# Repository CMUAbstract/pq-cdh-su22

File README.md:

# Pocketqube Command and Data Handling Board

Pocketqube command and data handling board

**Dependencies**

```bash
sudo apt install build-essential cmake gcc git libusb-1.0-0 libusb-1.0-0-dev libgtk-3-dev
cd $HOME/git-repos/cote/scripts
./setup_dependencies.sh $HOME/sw
```

# Useful link

* [libopencm3](http://libopencm3.org/docs/latest/stm32l4/html/modules.html) : Open source firmware link STM

## Directory Contents

* [3d-models](3d-models/README.md): Contains copies of `.stp` 3D model files
* [components](components/README.md): Contains copies of `.lib` component files
* [datasheets](datasheets/README.md): Contains component datasheets
* [footprints](footprints/README.md): Contains copies of `.kicad_mod` footprint
  files
* [gerbers](gerbers/README.md): Contains the most recent set of Gerber files
* [kicad](kicad/README.md): Contains the KiCad project files
* [versions](versions/README.md): Contains `.zip` files of Gerber files
  submitted for manufacture
* [BOM.csv](BOM.csv): Bill of materials
* [LICENSE](LICENSE): License
* [NOTES.md](NOTES.md): Step-by-step instructions for setting up KiCad,
  designing the board, and exporting Gerber files for manufacture
* [README.md](README.md): This document

## License

Written by Bradley Denby  
Other contributors: None

## Update

PQ-CDH Version 0.1.0 : 

1. Transferred design scheamtic and PCB from Kicad5 to Kicad6
2. Mounting holes adjustment same as referred to comm-401 board.
3. Reduced board dimension 43 x 43 mm
4. Removing 5th Pin from upper and lower right

PQ-CDH Version 0.1.1

1. Changed VDD, GND, SWDIO, and SWCLK to lower left to right 4 pins
2. Changed "PQ CDH v0.1.0" to "PQ CDH v0.1.1"
3. Adjusted controller and Conn_02x06_Odd_Even, for mounting hole clearance.
4. Adjusted Conn_02x06_Odd_Even in vertically aligned along with aligned to top and bottom connector holes.
5. Addition of 4 testpads added between oscillator and its capacitor.

PQ-CDH Version 0.2.0

1. I2C3 SDA and SCL to pins 1 and 2 on the bottom header row
2. ADC to pin 3 on the bottom header row
3. unused GPIO to pins 4 and 5 on bottom header row

See the top-level [LICENSE](LICENSE) file for the license.

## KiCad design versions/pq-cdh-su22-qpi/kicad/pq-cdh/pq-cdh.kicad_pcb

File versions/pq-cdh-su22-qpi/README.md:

# Pocketqube Command and Data Handling Board

Pocketqube command and data handling board

**Dependencies**

```bash
sudo apt install build-essential cmake gcc git libusb-1.0-0 libusb-1.0-0-dev libgtk-3-dev
cd $HOME/git-repos/cote/scripts
./setup_dependencies.sh $HOME/sw
```

## Useful link

* [libopencm3](http://libopencm3.org/docs/latest/stm32l4/html/modules.html) : STM open source firmware link

## Directory Contents

* [3d-models](3d-models/README.md): Contains copies of `.stp` 3D model files
* [components](components/README.md): Contains copies of `.lib` component files
* [datasheets](datasheets/README.md): Contains component datasheets
* [footprints](footprints/README.md): Contains copies of `.kicad_mod` footprint
  files
* [gerbers](gerbers/README.md): Contains the most recent set of Gerber files
* [kicad](kicad/README.md): Contains the KiCad project files
* [versions](versions/README.md): Contains `.zip` files of Gerber files
  submitted for manufacture
* [BOM.csv](BOM.csv): Bill of materials
* [LICENSE](LICENSE): License
* [NOTES.md](NOTES.md): Step-by-step instructions for setting up KiCad,
  designing the board, and exporting Gerber files for manufacture
* [README.md](README.md): This document

## License

Written by Bradley Denby  
Other contributors: None

## Update

PQ-CDH Version 0.1.0 : 

1. Transferred design scheamtic and PCB from Kicad5 to Kicad6
2. Mounting holes adjustment same as referred to comm-401 board.
3. Reduced board dimension 43 x 43 mm
4. Removing 5th Pin from upper and lower right

PQ-CDH Version 0.1.1

1. Changed VDD, GND, SWDIO, and SWCLK to lower left to right 4 pins
2. Changed "PQ CDH v0.1.0" to "PQ CDH v0.1.1"
3. Adjusted controller and Conn_02x06_Odd_Even, for mounting hole clearance.
4. Adjusted Conn_02x06_Odd_Even in vertically aligned along with aligned to top and bottom connector holes.
5. Addition of 4 testpads added between oscillator and its capacitor.

PQ-CDH Version 0.2.0

1. I2C3 SDA and SCL to pins 1 and 2 on the bottom header row
2. ADC to pin 3 on the bottom header row
3. unused GPIO to pins 4 and 5 on bottom header row

See the top-level [LICENSE](LICENSE) file for the license.

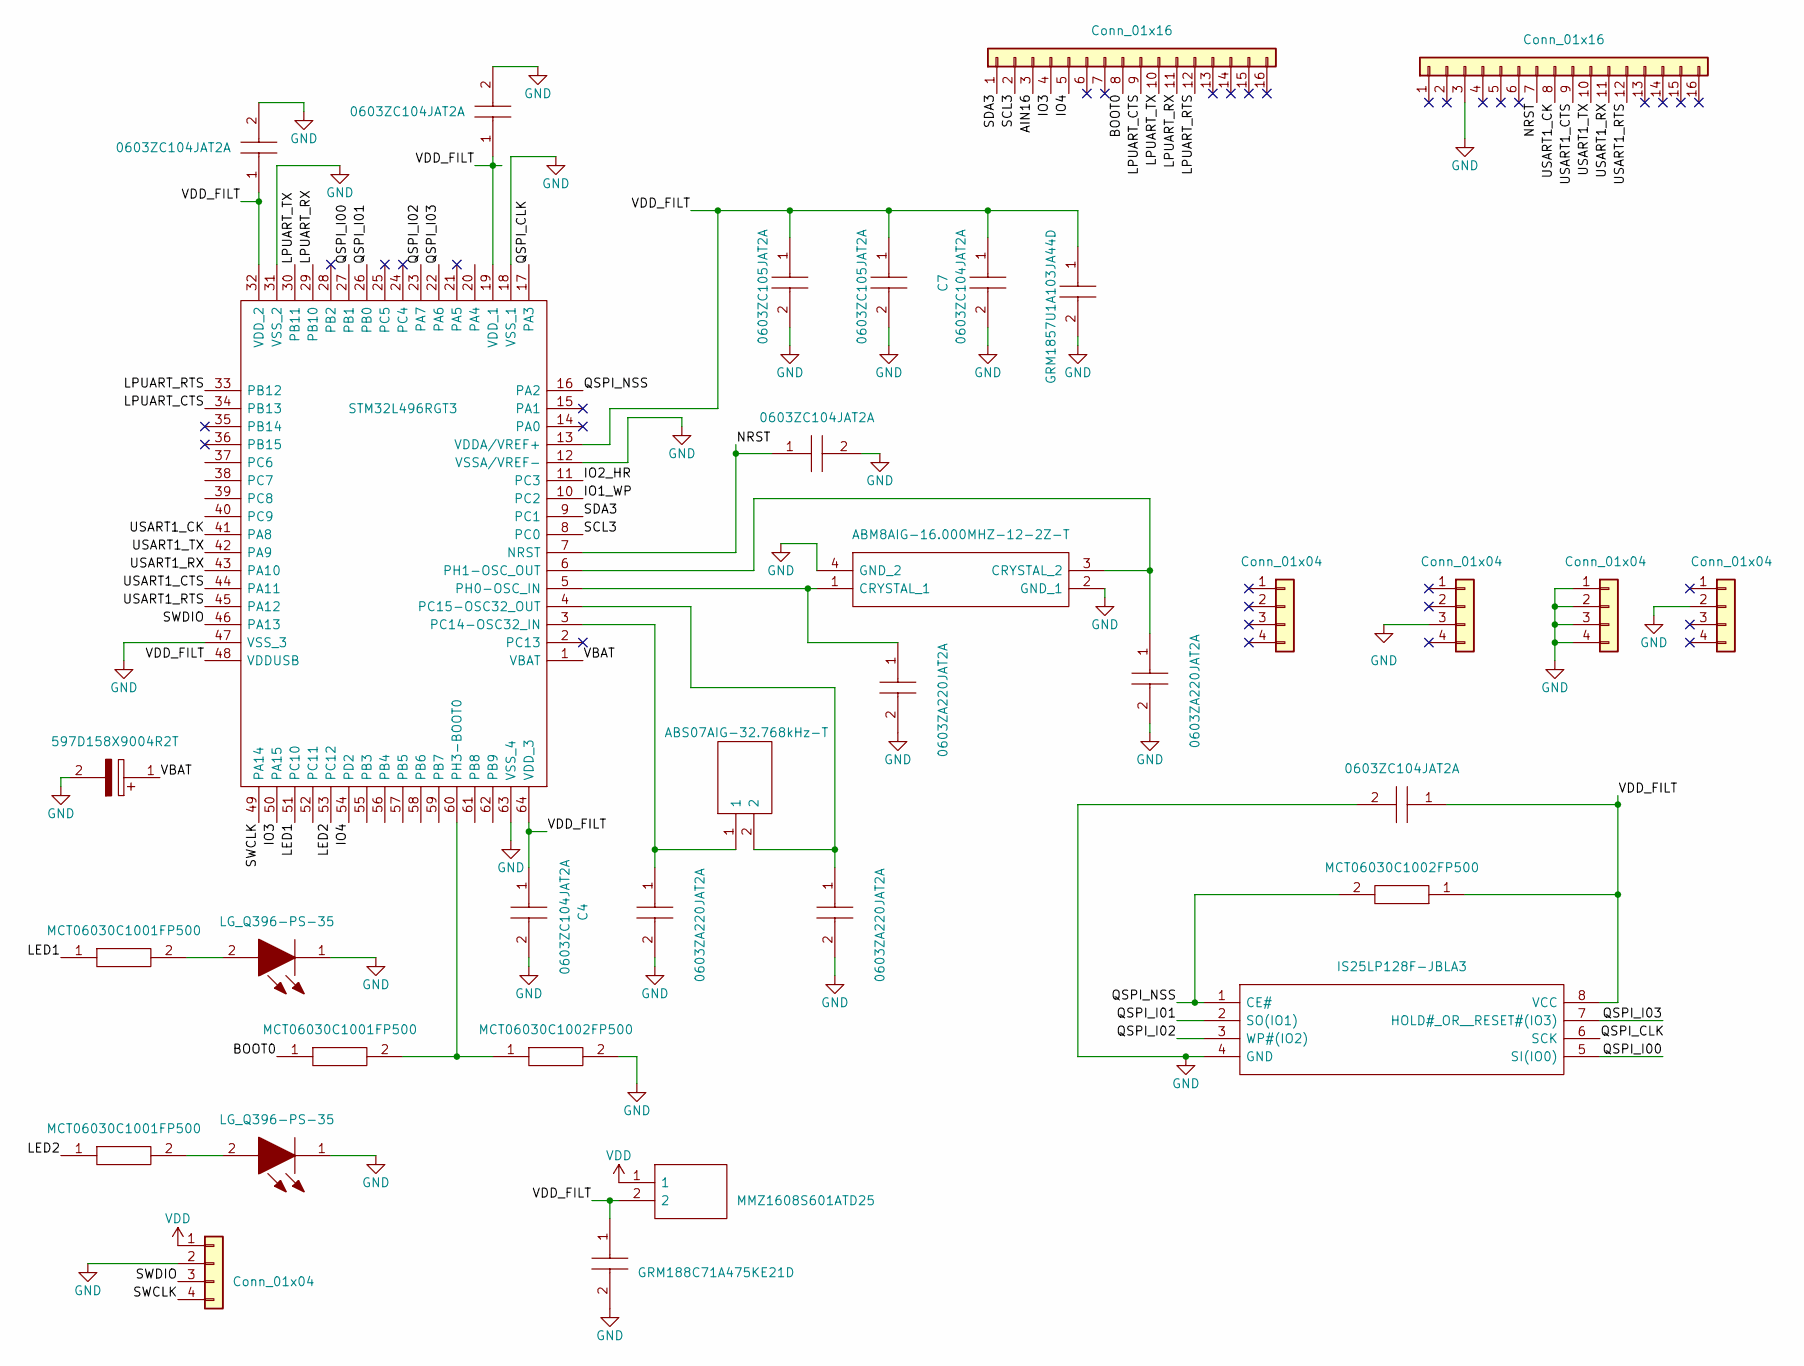
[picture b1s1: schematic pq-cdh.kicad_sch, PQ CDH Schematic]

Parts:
C1: GRM188C71A475KE21D; CAPC1608X90N; Manufacturer_Part_Number GRM188C71A475KE21D; Mouser Part Number 81-GRM188C71A475KE2D
C2, C3, C4, C7, C9, C14: 0603ZC104JAT2A; CAPC1608X90N; Manufacturer_Part_Number 0603ZC104JAT2A; Mouser Part Number 581-0603ZC104JAT2A
C5, C6: 0603ZC105JAT2A; CAPC1608X90N; Manufacturer_Part_Number 0603ZC105JAT2A; Mouser Part Number 581-0603ZC105JAT2A
C8: GRM1857U1A103JA44D; CAPC1608X50N; Manufacturer_Part_Number GRM1857U1A103JA44D; Mouser Part Number 81-GRM1857U1A103JA4D
C10, C11, C12, C13: 0603ZA220JAT2A; CAPC1608X90N; Manufacturer_Part_Number 0603ZA220JAT2A; Mouser Part Number 581-0603ZA220JAT2A
C15: 597D158X9004R2T; CAPPC5660X400N; Manufacturer_Part_Number 597D158X9004R2T; Mouser Part Number 71-597D158X9004R2T
FB1: MMZ1608S601ATD25; BEADC1608X95N; Manufacturer_Part_Number MMZ1608S601ATD25; Mouser Part Number 810-MMZ1608S601ATD25
IC1: STM32L496RGT3; QFP50P1200X1200X160-64N; Manufacturer_Part_Number STM32L496RGT3; Mouser Part Number 511-STM32L496RGT3
IC2: IS25LP128F-JBLA3; SOIC127P790X216-8N; Manufacturer_Part_Number IS25LP128F-JBLA3; Mouser Part Number 870-IS25LP128F-JBLA3
J1, J3, J4, J8: Conn_01x04; TartanArtibeus_PinSocket_1x4
J2, J5: Conn_01x16; TartanArtibeus_PinSocket_1x16
J6: Conn_01x04; TartanArtibeus_2021_MountingHoles
LED1, LED2: LG_Q396-PS-35; LGQ396PS35; Manufacturer_Part_Number LG Q396-PS-35; Mouser Part Number 720-LGQ396A3964
R1, R2, R4: MCT06030C1001FP500; RESC1608X55N; Manufacturer_Part_Number MCT06030C1001FP500; Mouser Part Number 594-MCT06030C1001FP5
R3, R5: MCT06030C1002FP500; RESC1608X55N; Manufacturer_Part_Number MCT06030C1002FP500; Mouser Part Number 594-MCT06030C1002FP5
Y1: ABM8AIG-16.000MHZ-12-2Z-T; ABM8AIG25000MHZ122ZT3; Manufacturer_Part_Number ABM8AIG-16.000MHZ-12-2Z-T; Mouser Part Number 815-ABM8AIG16122ZT
Y2: ABS07AIG-32.768kHz-T; ABS07AIG32768kHz71T; Manufacturer_Part_Number ABS07AIG-32.768kHz-T; Mouser Part Number 815-S07AIG-32.768T

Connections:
/AIN16: J2.3
/BOOT0: J2.8, R4.1
/IO1_WP: IC1.10 (PC2)
/IO2_HR: IC1.11 (PC3)
/IO3: IC1.50 (PA15), J2.4
/IO4: IC1.54 (PD2), J2.5
/LED1: IC1.51 (PC10), R1.1
/LED2: IC1.53 (PC12), R2.1
/LPUART_CTS: IC1.34 (PB13), J2.9
/LPUART_RTS: IC1.33 (PB12), J2.12
/LPUART_RX: IC1.29 (PB10), J2.11
/LPUART_TX: IC1.30 (PB11), J2.10
/NRST: C9.1, IC1.7 (NRST), J5.7
/QSPI_CLK: IC1.17 (PA3), IC2.6 (SCK)
/QSPI_I00: IC1.27 (PB1), IC2.5 (SI(IO0))
/QSPI_I01: IC1.26 (PB0), IC2.2 (SO(IO1))
/QSPI_I02: IC1.23 (PA7), IC2.3 (WP#(IO2))
/QSPI_I03: IC1.22 (PA6), IC2.7 (HOLD#_OR__RESET#(IO3))
/QSPI_NSS: IC1.16 (PA2), IC2.1 (CE#), R5.2
/SCL3: IC1.8 (PC0), J2.2
/SDA3: IC1.9 (PC1), J2.1
/SWCLK: IC1.49 (PA14), J1.4
/SWDIO: IC1.46 (PA13), J1.3
/USART1_CK: IC1.41 (PA8), J5.8
/USART1_CTS: IC1.44 (PA11), J5.9
/USART1_RTS: IC1.45 (PA12), J5.12
/USART1_RX: IC1.43 (PA10), J5.11
/USART1_TX: IC1.42 (PA9), J5.10
/VBAT: C15.1, IC1.1 (VBAT)
/VDD_FILT: C1.1, C2.1, C3.1, C4.1, C5.1, C6.1, C7.1, C8.1, C14.1, FB1.2, IC1.13 (VDDA/VREF+), IC1.19 (VDD_1), IC1.32 (VDD_2), IC1.48 (VDDUSB), IC1.64 (VDD_3), IC2.8 (VCC), R5.1
GND: C1.2, C2.2, C3.2, C4.2, C5.2, C6.2, C7.2, C8.2, C9.2, C10.2, C11.2, C12.2, C13.2, C14.2, C15.2, IC1.12 (VSSA/VREF-), IC1.18 (VSS_1), IC1.31 (VSS_2), IC1.47 (VSS_3), IC1.63 (VSS_4), IC2.4 (GND), J1.2, J4.3, J5.3, J6.1, J6.2, J6.3, J6.4, J8.2, LED1.1, LED2.1, R3.2, Y1.2 (GND_1), Y1.4 (GND_2)
unnamed 31: C10.1, IC1.6 (PH1-OSC_OUT), Y1.3 (CRYSTAL_2); also elsewhere on the board
unnamed 32: C11.1, IC1.5 (PH0-OSC_IN), Y1.1 (CRYSTAL_1); also elsewhere on the board
unnamed 33: C12.1, IC1.4 (PC15-OSC32_OUT), Y2.2; also elsewhere on the board
unnamed 34: C13.1, IC1.3 (PC14-OSC32_IN), Y2.1; also elsewhere on the board
unnamed: IC1.60 (PH3-BOOT0), R3.1, R4.2
unnamed: LED1.2, R1.2
unnamed: LED2.2, R2.2
VDD: FB1.1, J1.1

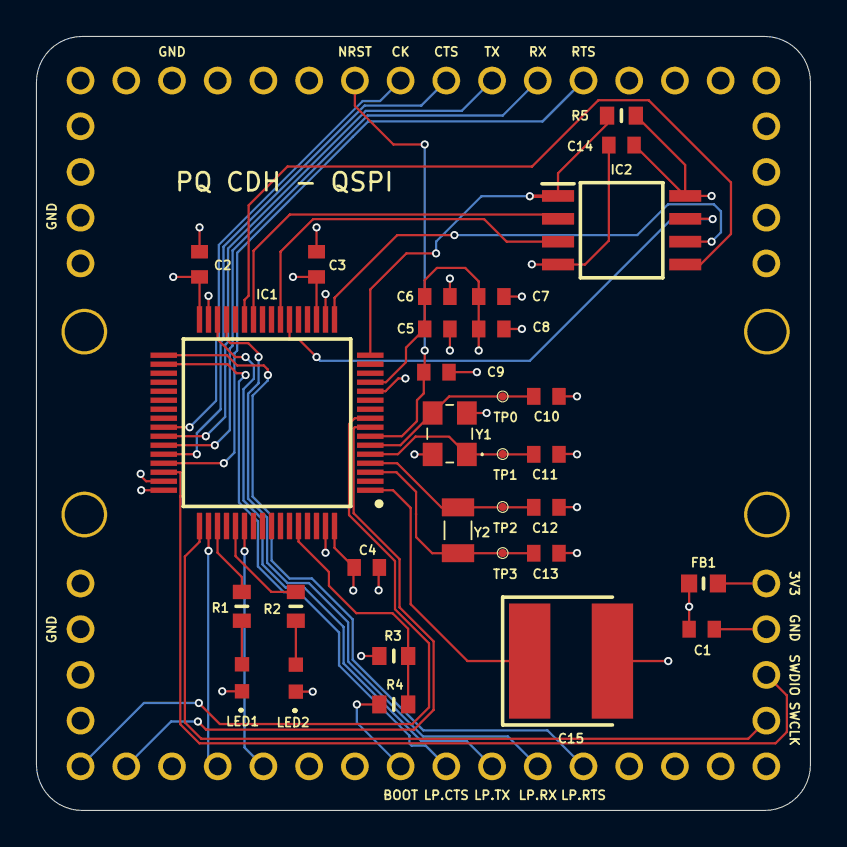
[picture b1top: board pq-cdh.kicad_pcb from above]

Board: 4 copper layers, 43.0 x 43.0 mm, 36 parts (0 on the bottom side), 36 nets.

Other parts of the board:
TP: TP2; TestPoint_Pad_D1.0mm
TP#2: TP1; TestPoint_Pad_D1.0mm
TP#3: TP0; TestPoint_Pad_D1.0mm
TP#4: TP3; TestPoint_Pad_D1.0mm

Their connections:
unnamed 31: TP#3.1; also elsewhere on the board
unnamed 32: TP#2.2; also elsewhere on the board
unnamed 33: TP.3; also elsewhere on the board
unnamed 34: TP#4.4; also elsewhere on the board

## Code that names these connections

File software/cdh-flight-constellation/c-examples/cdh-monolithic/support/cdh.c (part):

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  rcc_periph_clock_enable(RCC_GPIOA);
  rcc_periph_clock_enable(RCC_USART1);
  gpio_mode_setup(GPIOA,GPIO_MODE_AF,GPIO_PUPD_NONE,GPIO9|GPIO10);
  gpio_set_af(GPIOA,GPIO_AF7,GPIO9);  // USART1_TX is alternate function 7
  gpio_set_af(GPIOA,GPIO_AF7,GPIO10); // USART1_RX is alternate function 7
  usart_set_baudrate(USART1,115200);
  usart_set_databits(USART1,8);
  usart_set_stopbits(USART1,USART_STOPBITS_1);
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    uint8_t b = pop_tx_cmd_buff(tx_cmd_buff_o);      // Pop byte from TX buffer
    usart_send(USART1,b);                            // Send byte to TX pin
    if(tx_cmd_buff_o->empty) {                       // if TX buffer empty
      gpio_toggle(GPIOC, GPIO10);                    //  Toggle LED1
      gpio_toggle(GPIOC, GPIO12);                    //  Toggle LED2
    }                                                //
  }                                                  //
}
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
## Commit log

2022-05-26 Adds essential files and directories
2022-05-31 3D_Models_build_V1.0.1
2022-05-31 Components_lib_build_V1.0.1
2022-05-31 Kicad_mod_build_v1.0.1
2022-05-31 Gerber_Build_output_v1.0.1
2022-05-31 pq-cdh_build_schematic_pcb_v1.0.1
    PCB, Schematic, Symbol, Project File
2022-05-31 kicad_mod_footprints_v1.0.1
2022-05-31 version_1.0.1_build_output
2022-05-31 pq_cdh_BOM_v1.0.1
2022-05-31 Datasheet_v1.0.1
2022-06-01 With Changes related Ext Flash SPI configuration
2022-06-01 Added crystal Oscillator 3D models
2022-06-01 With Xtal 3D-models
2022-06-01 Silkscreen_room update for IC2 and C15
2022-06-01 Silkscreen nameupdate for IC2 and C15
2022-06-02 MountingHole_adjustment
2022-06-02 MountingHoles_adjustment
2022-06-03 review_updates
2022-06-03 Review_update_mountingHole_Clearance
2022-06-03 Updated_BOM sheet v0.1.0
2022-06-03 latest_gerbers file
2022-06-03 gerbers
2022-06-03 Final_gerber_update
2022-06-03 version_name_update
2022-06-03 gerber_update
2022-06-03 Updated_BOM
    With first order placed
2022-06-03 Updated_BOM
    first order placed
2022-06-03 v0.1.0_order_placed
2022-06-07 Added Order_status column
2022-06-09 v0.2.0
    Controller_adjustment
2022-06-09 v0.1.1_updates
2022-06-09 version_v0.1.1_ReadMe_update
2022-06-09 test_pad_addition
2022-06-10 v0.1.1_review_updates
    remove vias for SWDIO and SWCLK and connecting directly to lower right connectors
2022-06-10 v0.1.1_review_updates
    remove vias for SWDIO and SWCLK
2022-06-10 Unused_Pins_v0.1.1
2022-06-10 pd-cdh_v0.1.1
    PCB ordered
2022-06-16 pd_cdh_v0.2.0
    - I2C3 SDA and SCL to pins 1 and 2 on the bottom header row
    - ADC to pin 3 on the bottom header row
    - unused GPIO to pins 4 and 5 on the bottom header row
2022-06-16 ReadMe_update_v0.2.0
2022-06-16 PINs_details_sheet
2022-06-16 Pin_details_sheet
2022-06-16 pd_cdh_v0.2.0_review_updates
2022-06-16 pd-cdh_v0.2.0
2022-07-15 Adds software support
2022-09-15 Sync lab-computer software
2022-09-19 Added tests for transmission of TAB commands from CDH board
2022-09-20 MVP Spi flash chip -- somewhat buggy
2022-09-29 Test-code for external HSE oscillator
    High-speed oscillator - 25MHz
2022-09-29 support library for HSE test-code
2022-09-29 make file
    make file configured for HSE build
2022-09-29 test-code for internal PLL
    LSI internal clock 16MHz
2022-09-29 library support file for LSI build
2022-10-03 updated_HSE
2022-10-03 support file
2022-10-03 int pll
2022-10-03 Updated git-ignore and added stm32 reference manual
2022-10-03 Cleaned libopencm3 and DS_Store files
2022-10-06 cleanup
2022-10-10 quad spi demo WIP
2022-10-30 Update Nrf_linker_configuration_W_NW_test
2022-10-30 HSE clocked @ 100MHz
2022-10-30 HSE derived PLL clock output 100 MHz
2022-10-30 PLL clock source derived from internal HSI
2022-10-30 internal HSI configuration
2022-11-03 Updates to QSPI demo
2022-11-03 QSPI version
2022-12-08 Added version of cdh board utilizing updated tab.c/.h files
2022-12-22 st-link setup with different git commit version
2023-01-11 eps+cpm+cdh
2023-05-03 initial_version
2023-05-03 Initial version
2023-05-03 Added HWID filter 0x5441 for constellation
2023-05-03 Added support to HWIDs based communication with constellation

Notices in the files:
software/cdh-flight-constellation/c-examples/cdh-monolithic/support/cdh.c:
See the top-level LICENSE file for the license.
